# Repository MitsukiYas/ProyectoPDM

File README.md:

# ProyectoPDM
CarroTransbordador.pdf -> Esquemático y CarroTransbordador.step -> Modelo de la PCB

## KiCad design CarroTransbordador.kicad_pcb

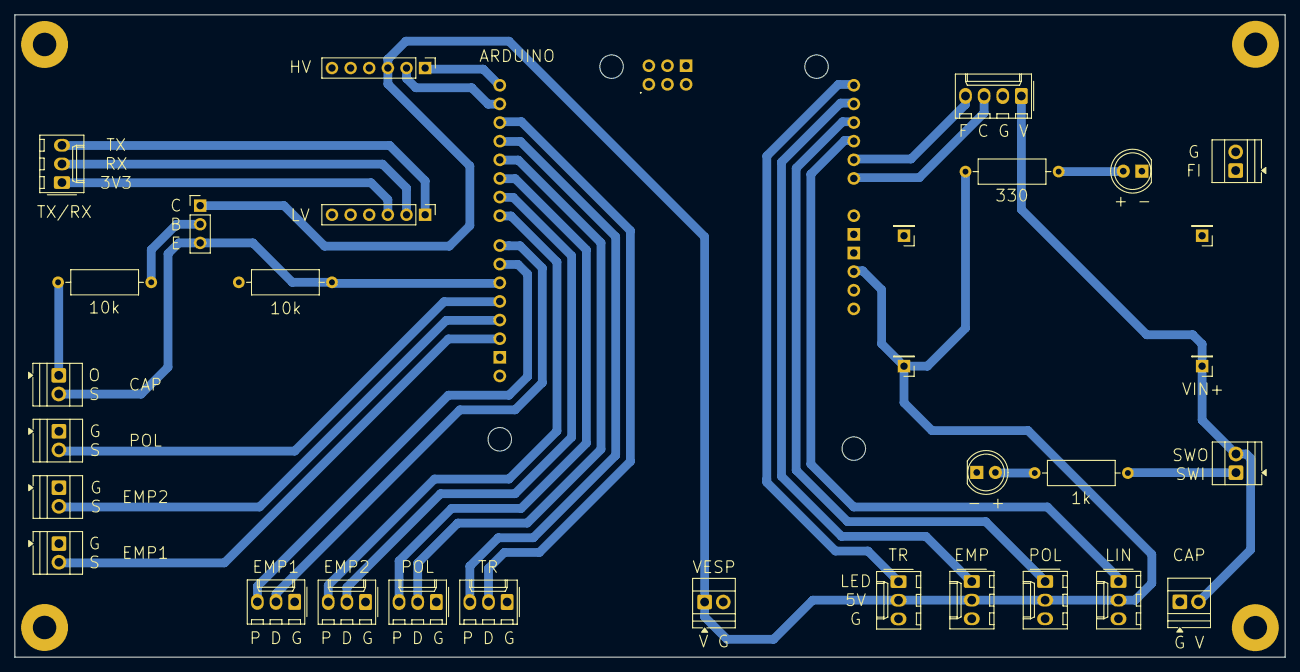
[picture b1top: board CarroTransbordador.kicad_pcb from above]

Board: 2 copper layers, 173.2 x 87.6 mm, 32 parts (0 on the bottom side), 31 nets.

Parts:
A1: Arduino UNO; Arduino_Uno_R2_Shield
D1, D2: LED; LED_D5.0mm
J4: Borner 12V 6A; TerminalBlock_Xinya_XY308-2.54-2P_1x02_P2.54mm_Horizontal
J8: Conn. BJT; PinHeader_1x03_P2.54mm_Vertical
J9: VIN+ Pin; PinHeader_1x01_P2.54mm_Vertical
J10: VIN- Pin; PinHeader_1x01_P2.54mm_Vertical
J11: VOUT+ Pin; PinHeader_1x01_P2.54mm_Vertical
J12: VOUT- Pin; PinHeader_1x01_P2.54mm_Vertical
J13: Borner ESP32; TerminalBlock_Xinya_XY308-2.54-2P_1x02_P2.54mm_Horizontal
J14: Conn. Conv. HV; PinHeader_1x06_P2.54mm_Vertical
J15: Conn. Conv. LV; PinHeader_1x06_P2.54mm_Vertical
J16: Conn. ESP32; Molex_KK-254_AE-6410-03A_1x03_P2.54mm_Vertical
J17: Conn. LED Tr.; Molex_KK-254_AE-6410-03A_1x03_P2.54mm_Vertical
J18: Conn. LED Empot.; Molex_KK-254_AE-6410-03A_1x03_P2.54mm_Vertical
J19: Conn. LED Polea; Molex_KK-254_AE-6410-03A_1x03_P2.54mm_Vertical
J20: Conn. LED Lineal; Molex_KK-254_AE-6410-03A_1x03_P2.54mm_Vertical
J21: Conn. Ctrl. Tr.; Molex_KK-254_AE-6410-03A_1x03_P2.54mm_Vertical
J22: Conn. Ctrl. Polea; Molex_KK-254_AE-6410-03A_1x03_P2.54mm_Vertical
J23: Conn. Ctrl. Empot. 2; Molex_KK-254_AE-6410-03A_1x03_P2.54mm_Vertical
J24: Conn. Ctrl. Empot. 1; Molex_KK-254_AE-6410-03A_1x03_P2.54mm_Vertical
J26: Conn. Lineal; Molex_KK-254_AE-6410-04A_1x04_P2.54mm_Vertical
J27: Borner Ctrl. Empot. 1; TerminalBlock_Xinya_XY308-2.54-2P_1x02_P2.54mm_Horizontal
J28: Borner Ctrl. Empot. 2; TerminalBlock_Xinya_XY308-2.54-2P_1x02_P2.54mm_Horizontal
J29: Borner Ctrl. Polea; TerminalBlock_Xinya_XY308-2.54-2P_1x02_P2.54mm_Horizontal
J30: Borner Capacitor 1; TerminalBlock_Xinya_XY308-2.54-2P_1x02_P2.54mm_Horizontal
J31: Borner Capacitor 2; TerminalBlock_Xinya_XY308-2.54-2P_1x02_P2.54mm_Horizontal
J40: Borner Switch IN; TerminalBlock_Xinya_XY308-2.54-2P_1x02_P2.54mm_Horizontal
R1: 1k; R_Axial_DIN0309_L9.0mm_D3.2mm_P12.70mm_Horizontal
R2: 330; R_Axial_DIN0309_L9.0mm_D3.2mm_P12.70mm_Horizontal
R3, R4: 10k; R_Axial_DIN0309_L9.0mm_D3.2mm_P12.70mm_Horizontal

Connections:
+5V: A1.5V1 (5V), J8.1, J11.1, J13.1, J14.3, J17.2, J18.2, J19.2, J20.2, R2.1
+12V6A: J40.1, R1.1
/ModuloActuadores/CTRL_LINEAR: A1.A0, J26.3
/ModuloActuadores/FD_LINEAR: A1.A1, J26.4
/ModuloActuadores/PWR_LINEAR: J9.1, J26.1, J30.2, J40.2
/ModuloControladores/3V3_ESP: J15.3, J16.1
/ModuloControladores/DIR_MOTOR_EMPOT1: A1.D8, J24.2
/ModuloControladores/DIR_MOTOR_EMPOT2: A1.D6, J23.2
/ModuloControladores/DIR_MOTOR_POLEA: A1.D4, J22.2
/ModuloControladores/DIR_MOTOR_TR: A1.D2 (D2_INT0), J21.2
/ModuloControladores/FDC_EMPOT1: A1.D13, J27.2
/ModuloControladores/FDC_EMPOT2: A1.D12, J28.2
/ModuloControladores/FDC_POLEA: A1.D11, J29.2
/ModuloControladores/PIN_LED_EMPOT: A1.A4 (A4/SDA), J18.1
/ModuloControladores/PIN_LED_LINEAR: A1.A2, J20.1
/ModuloControladores/PIN_LED_POLEA: A1.A3, J19.1
/ModuloControladores/PIN_LED_TR: A1.A5 (A5/SCL), J17.1
/ModuloControladores/PUL_MOTOR_EMPOT1: A1.D9, J24.3
/ModuloControladores/PUL_MOTOR_EMPOT2: A1.D7, J23.3
/ModuloControladores/PUL_MOTOR_POLEA: A1.D5, J22.3
/ModuloControladores/PUL_MOTOR_TR: A1.D3 (D3_INT1), J21.3
/ModuloControladores/SERIAL_RX_ARD: A1.D0 (D0/RX), J14.1
/ModuloControladores/SERIAL_RX_ESP: J15.2, J16.2
/ModuloControladores/SERIAL_TX_ARD: A1.D1 (D1/TX), J14.2
/ModuloControladores/SERIAL_TX_ESP: J15.1, J16.3
/ModuloControladores/SIGNAL_CAP: A1.D10 (D10_CS), J8.3, J31.2, R4.1
/ModuloSensores/BASE_BJT: J8.2, R3.1
/ModuloSensores/OUT_CAP: J31.1, R3.2
GNDS: A1.GND1 (GND), A1.GND2 (GND), D1.1 (K), D2.1 (K), J4.2, J10.1, J12.1, J13.2, J14.4, J15.4, J17.3, J18.3, J19.3, J20.3, J21.1, J22.1, J23.1, J24.1, J26.2, J27.1, J28.1, J29.1, J30.1, R4.2
unnamed: D1.2 (A), R1.2
unnamed: D2.2 (A), R2.2

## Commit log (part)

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2026-06-20 Primer commit
2026-06-25 Version mandada para PCB
2026-06-25 Nuevo step y pdf
2026-06-25 Interfaz ESP32
2026-06-25 Codigo Arduino
2026-06-26 sch corregido
